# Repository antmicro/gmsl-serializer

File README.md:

# GMSL Serializer Board

Copyright (c) 2023-2025 [Antmicro](https://www.antmicro.com)

## Overview

This project contains open hardware design files for the GMSL Serializer Board.
This board accepts MIPI CSI-2 signals from Antmicro's 50-pin FFC video interface and transmits the video data over GMSL2.
The GMSL Serializer Board is powered over GMSL coaxial cable.

The design files were prepared in KiCad 8.

## Key features

* Input: 4-lane MIPI CSI-2 interface on a 50-pin Antmicro Dual Camera connector
* Output: GMSL2 interface exposed on a FAKRA connector
* PoC filter for sinking power from the GMSL coaxial cable

## Project structure

The main project directory contains KiCad PCB project files, a LICENSE, and a README.
The remaining files are stored in the following directories:

* `doc` - contains schematics
* `assets` - contains visual assets for showcasing the board on Antmicro [Open Hardware Portal](https://openhardware.antmicro.com)

## Licensing

This project is published under the [Apache-2.0](LICENSE) license.

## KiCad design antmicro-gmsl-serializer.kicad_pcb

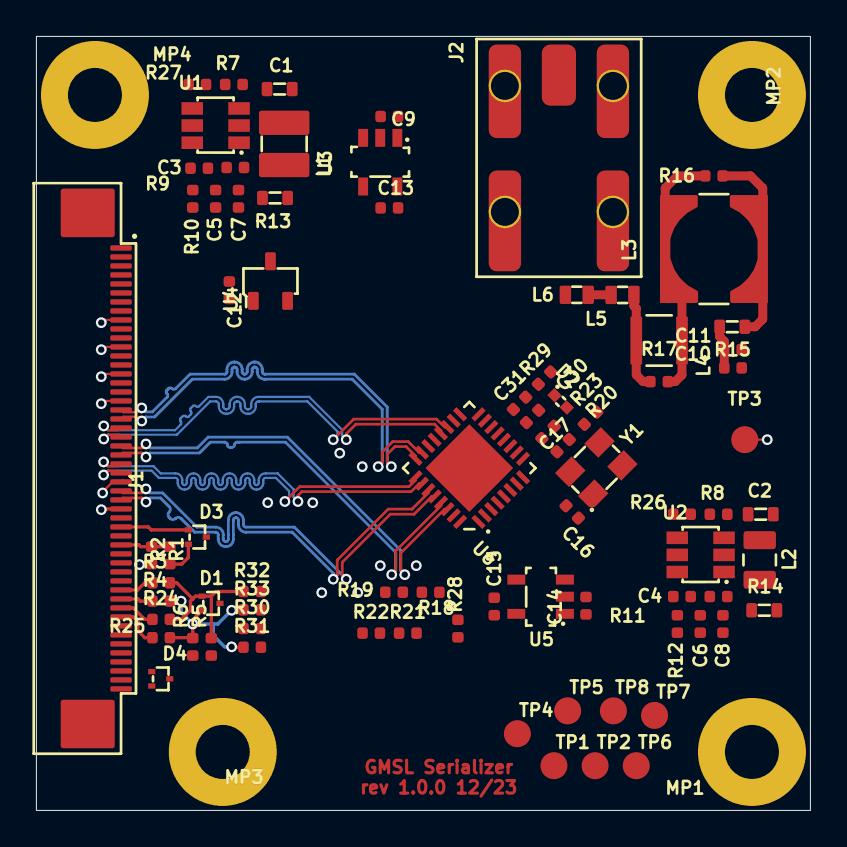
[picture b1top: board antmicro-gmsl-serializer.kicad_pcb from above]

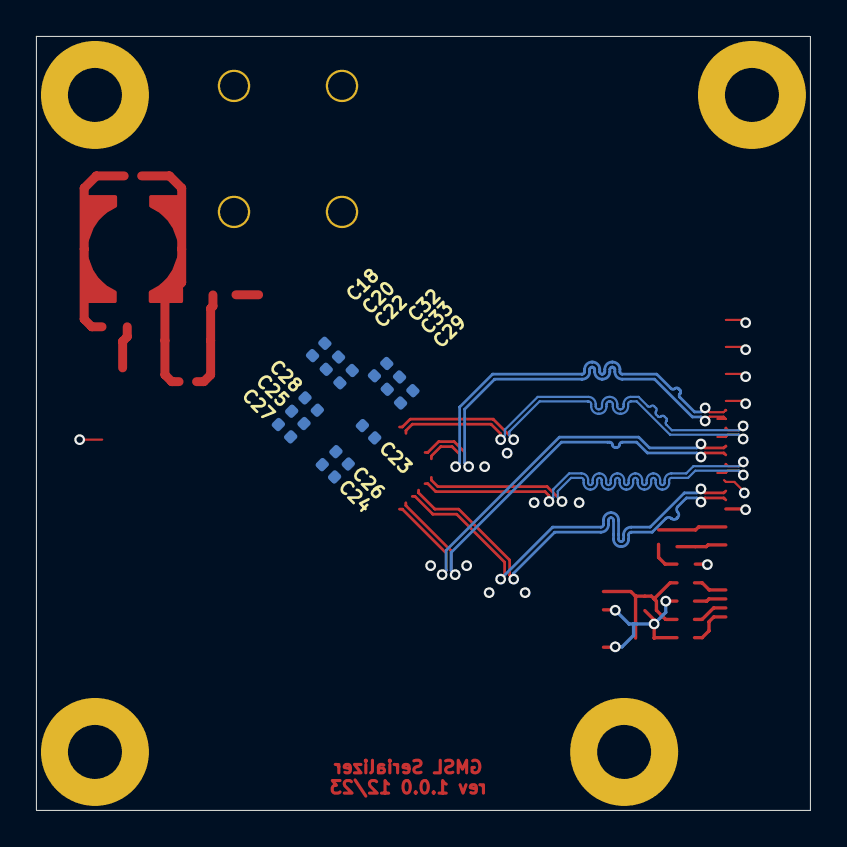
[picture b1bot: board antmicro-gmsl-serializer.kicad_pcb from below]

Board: 4 copper layers, 43.0 x 43.0 mm, 95 parts (12 on the bottom side), 60 nets.

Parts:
C1, C2: C_10u_25V_0603; C_0603_1608Metric
C3: C_220n_0402; C_0402_1005Metric
C4, C10, C20, C22, C24, C30, C31: C_100n_0402; C_0402_1005Metric
C5, C6, C7, C8: C_22u_0402; C_0402_1005Metric
C9, C12, C13, C14, C15: C_1u_16V_0402; C_0402_1005Metric
C11, C23, C27, C28, C29, C32: C_10n_0402; C_0402_1005Metric
C16, C17: C_33p_0402; C_0402_1005Metric
C18, C25, C26, C33: C_10u_0402; C_0402_1005Metric
D1, D3, D4: TPD2E009_SOT-9X3; SOT-723
D2: AXGD10402KR; D_0402_1005Metric
J1: Conn_FFC_WE_68715014022; Conn_FFC_WE_68715014x22
J2: Conn_FAKRA_2FAI-NZSP-PCBB6; Conn_FAKRA_59S2AQ-40MT5-Z_1
L1: L_3u3_3.1A_Bourns-SRP3212A; L_Bourns-SRP3212A
L2: L_1u_2.6A_0806; L_0806_2016Metric
L3: L_22u_1.12A_Coilcraft-MSS6132T; L_Coilcraft-MSS6132T
L4: L_6u8_1A_Coilcraft-1210POC; L_Coilcraft-1210POC
L5, L6: L_470n_1A_Coilcraft-PFL1609; L_Coilcraft-PFL1609
MP1, MP2, MP3, MP4: MP_Pad6mm_Drill3mm
R1, R7, R8, R10, R12, R19, R22, R26, R27, R28: R_10k_0402; R_0402_1005Metric
R2: R_12k_0402; R_0402_1005Metric
R3, R4, R24, R25: R_100R_0402; R_0402_1005Metric
R5, R6: R_4k7_0402; R_0402_1005Metric
R9: R_52k3_0402; R_0402_1005Metric
R11: R_12k4_0402; R_0402_1005Metric
R13, R14, R15: R_0R_22.4A_0603; R_0603_1608Metric
R16, R17: R_5k1_0402; R_0402_1005Metric
R18, R21: R_80k6_0402; R_0402_1005Metric
R20, R30, R31, R32, R33: R_0R_0402; R_0402_1005Metric
R23: R_402R_0402; R_0402_1005Metric
R29: R_51R_0402; R_0402_1005Metric
TP1, TP2, TP3, TP4, TP5, TP6, TP7, TP8: TP_1.5mm_SMD; TP_SMD_1.5mm
U1, U2: AP62301_TSOT; TSOT23-6
U3: NCP163ASN330T1G; SOT-23-5
U4: REF3012AIDBZT; SOT-23-3
U5: TLV73312PDBVT; SOT-23-5
U6: MAX9295A; QFN-32-1EP_5x5mm
Y1: Resonator_25MHz_ABM8G; Oscillator_SMD_Geyer_KX-7-4Pin_3.2x2.5mm

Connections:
+1V2: C15.2, C18.2, C20.2, C22.2, TP5.1, U5.5 (VOUT), U6.15 (VDD)
+1V8: C14.2, C25.2, C27.2, C28.2, R14.2, TP2.1, U5.1 (VIN), U5.3 (EN), U6.11 (VDD_1.8V)
+3V3: C13.2, C29.2, C32.2, C33.2, D4.1, J1.47, J1.48, R5.2, R6.2, R28.2, TP4.1, U3.5 (VOUT), U6.16 (VDDIO)
+5V: C9.2, C12.2, D4.2, J1.49, J1.50, R13.2, TP1.1, U3.1 (VIN), U3.3 (EN), U4.1 (IN)
+12V: C1.2, C2.2, C10.2, C11.2, R7.2, R8.2, R15.1, TP3.1, U1.3 (VIN), U2.3 (VIN)
/Connectors/SCL_CAM0: J1.40, R4.1
/Connectors/SCL_CAM1: J1.42, R25.1
/Connectors/SDA_CAM0: J1.39, R3.1
/Connectors/SDA_CAM1: J1.41, R24.1
/Serializer/CFG0: R18.1, R19.2, U6.3 (MFP1/CFG0)
/Serializer/CFG1: R21.1, R22.2, U6.4 (MFP2/CFG1)
/Serializer/VDDIO: R18.2, R21.2
/Serializer/X1: C16.2, U6.8 (X1/OSC), Y1.1
/Serializer/X2: R20.2, U6.9 (X2)
/Serializer/X2_R: C17.2, R20.1, Y1.3
/Supply/EN_1V8: R8.1, R26.2, U2.5 (EN)
/Supply/EN_5V: R7.1, R27.2, U1.5 (EN)
/Supply/FB_1V8: R11.1, R12.2, U2.4 (FB)
/Supply/FB_5V: R9.1, R10.2, U1.4 (FB)
/Supply/OUT_1V8: C6.2, C8.2, L2.2, R11.2, R14.1
/Supply/OUT_5V: C5.2, C7.2, L1.2, R9.2, R13.1
/Supply/SW_1V8: C4.2, L2.1, U2.2 (SW)
/Supply/SW_5V: C3.2, L1.1, U1.2 (SW)
CSI_CLK_N: J1.28, U6.28 (CK_N)
CSI_CLK_P: J1.29, U6.27 (CK_P)
CSI_D0_N: J1.25, U6.26 (D0_N)
CSI_D0_P: J1.26, U6.25 (D0_P)
CSI_D1_N: J1.23, U6.30 (D1_N)
CSI_D1_P: J1.24, U6.29 (D1_P)
CSI_D2_N: J1.21, U6.20 (D2_N)
CSI_D2_P: J1.22, U6.19 (D2_P)
CSI_D3_N: J1.19, U6.24 (D3_N)
CSI_D3_P: J1.20, U6.23 (D3_P)
GND: C1.1, C2.1, C5.1, C6.1, C7.1, C8.1, C9.1, C10.1, C11.1, C12.1, C13.1, C14.1, C15.1, C16.1, C17.1, C18.1, C20.1, C22.1, C23.1, C24.1, C25.1, C26.1, C27.1, C28.1, C29.1, C32.1, C33.1, D1.3, D2.2, D3.3, D4.3, J1.9, J1.12, J1.15, J1.18, J1.27, J1.30, J1.MP1 (MP), J1.MP2 (MP), J2.2, J2.3, J2.4, J2.5, MP1.1, MP2.1, MP3.1, MP4.1, R2.2, R10.1, R12.1, R19.1, R22.1, R23.1, R26.1, R27.1, R29.1, U1.1 (GND), U2.1 (GND), U3.2 (GND), U4.3 (GND), U5.2 (GND), U6.33 (GND), Y1.2 (SH), Y1.4 (SH)
GPIO3: D3.1, J1.32, U6.17 (MFP3)
GPIO4: D3.2, R1.2, U6.18 (MFP4)
unnamed: C3.1, U1.6 (BST)
unnamed: C4.1, U2.6 (BST)
unnamed: C23.2, C24.2, C26.2, U6.14 (CAP_VDD)
unnamed: C30.1, U6.12 (SIO_P)
unnamed: C31.1, U6.13 (SIO_N)
unnamed: C31.2, R29.2
unnamed: J1.34, R1.1, R2.1
unnamed: L3.1, R15.2, R16.1
unnamed: L3.2, L4.1, R16.2, R17.1
unnamed: L4.2, L5.1, R17.2
unnamed: L5.2, L6.1
unnamed: R23.2, U6.10 (XRES)
unnamed: R28.1, U6.1 (PWDNB)
unnamed: R30.2, U6.31 (MFP7)
unnamed: R31.2, U6.32 (MFP8)
unnamed: R32.2, U6.5 (MFP9)
unnamed: R33.2, U6.6 (MFP10)
unnamed: TP6.1, U6.2 (MFP0)
unnamed: TP7.1, U6.21 (MFP5)
unnamed: TP8.1, U6.22 (MFP6)
SCL: D1.2, R4.2, R6.1, R25.2, R31.1, R33.1
SDA: D1.1, R3.2, R5.1, R24.2, R30.1, R32.1
SIO_P: C30.2, D2.1, J2.1, L6.2
VREF: U4.2 (OUT), U6.7 (VREF)

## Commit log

2023-11-28 Add .gitignore
2024-01-11 Implement changes suggested in design review to schematics
2024-01-11 Import layer stack, add mounting points
2024-01-11 Remove #auto_saved_files#
2024-01-11 Add Antmicro and OShw logos
2024-01-11 Add 1V8 to 1V2 LDO
2024-01-11 Place and route I2C components
2024-01-11 Place and route DC converters
2024-01-11 Add block diagram to schematic
2024-01-11 Change VDDIO to 3V3
2024-01-11 Place and route chip decoupling caps and oscillator
2024-01-11 Add resistor selectable i2c
2024-01-11 Add LICENSE
2024-01-11 Add crystal to the serializer chip
2024-01-11 [WiP]:Add serializer signals and decoupling capacitors
2024-01-11 Add stiching vias and GND planes
2024-01-11 Add I2C protection
2024-01-11 Update stackup
2024-01-11 Route CSI lines
2024-01-11 Add 2V5 VREF
2024-01-11 Add PoC, 5V converter, 1V8 converter
2024-01-11 Import changes from schematic to PCB, place additional components
2024-01-11 Draw board outline, place MPs and 50pin conn
2024-01-11 Add i2c and gpio triggers
2024-01-11 Anotate components and fix ERC errors and warnings
2024-01-11 Add serializer supply filtration
2024-01-11 Add cfg pins handling
2024-01-11 Tune CSI lines
2024-01-11 Change revision on schematic to 1.0.0
2024-01-11 Add 5V -> 3V3 LDO to supply section
2024-01-11 Decrease board size
2024-01-11 Add 50 pin FFC cSI connector
2024-01-11 Add low-capacitance TVS to serial output
2024-01-11 Place and route PoC filter
2024-01-11 Add initial project
2024-01-11 Relocate DC converters and add planes
2024-01-11 Add testpoints to unused MF pins
2024-01-11 Add FAKRA connector
2024-01-11 Reference voltage chip closer to the Vref pin
2024-01-11 Route 12V to 5V DC converter
2024-01-11 Remove R15 and anotate schematic
2024-01-11 Clean DRC
2024-01-11 Route 12V to 1V8 DC converter
2024-01-11 Tune CSI tracks
2024-01-11 Update TVS diodes
2024-01-11 Make power tracks wider
2024-01-11 Round CSI tracks
2024-01-11 [#53377] Rearange supply schematic
2024-01-11 Move gmsl track to the middle of the pad
2024-01-11 Route serializer chip breakout
2024-01-11 Improve decoupling capacitors
2024-01-11 [#53377] Mark 1V25 reference as DNP
2024-01-11 [#52707] PCB: place designators, update footprints, clean ERC
2024-01-11 Make 5V track wider - 1mm)
2024-01-11 Allign schematic components
2024-01-11 Add PCB SHA silkscreen text
2024-01-11 [#53377] Add LDO config register addresses to schematic
2024-01-11 Change default track width 0.125 -> 0.2
2024-01-11 Remove leftover ERC exclusions
2024-01-11 Route I2C
2024-01-11 Update GND plane and date
2024-01-11 Improve layout
2024-01-11 Remove mounting points designators
2024-01-11 Improve L5 connection, improve ground plane
2024-01-11 Move cfg resistors further from CSI lines
2024-01-11 Route low speed signals
2024-01-11 Increase decoupling caps track width
2024-01-11 Add OHP assets
2024-01-12 Add initial README
2024-01-12 Update naming convention
2024-01-12 Add PDF schematic
2024-01-12 README: Add 3D Vis
2024-01-12 Rescale image
2024-02-07 Notes added by 'git notes add'
2024-06-21 [#55438] Add LED indicators to schematics
2024-06-21 [#55438] Place LED indicators on PCB
2024-06-24 [#55438] Update README.md
2024-06-24 [#55438] Add GND testpoint
2024-06-24 [#55438] Update FAKRA connector
2024-07-02 [#55438] Update assets, doc and img
2024-07-02 [#55438] Update components
2024-09-10 [#65118] Update assets
2024-10-04 [#66847] Make schematic hierarchical
2024-10-04 [#66847] Serializer chip: MAX9295A -> MAX96717
2024-10-07 [#66847] unDNP pullups on I2C; update pcb from sch
2024-10-07 [#66847] Update DNP style; Update from lib; Fix CSI bus definition
2024-10-07 [#66847] Change 3V3 LDO; Update L3 footprint
2024-10-07 [#66847] Start improving CSI layout
2024-10-08 [#66847] Tune CSI
2024-10-08 [#66847] Layout improvements
2024-10-08 [#66847] Bump date&rev; Clean ERC
2024-10-08 [#66847] Update config resistors
2024-10-08 [#66847] Show MPN insted value; Update description
2024-10-08 [#66847] Update MAX96717 symbol: flip CSI N/P to match symbol standard
2024-10-08 [#66847] Updated vias
2024-10-08 [#66847] Update assets
2024-11-25 [#69177] Update to Kicad 8
2024-11-25 [#69177] Switched 3V3 suply from LDO to buck converter
2024-11-25 [#69177] Updated layout with new buck converter
2024-11-25 [#69177] Routed changed components
2024-11-25 [#69177] Solved all DRC problems
2024-11-25 [#69177] Updated revision to 1.1.1
2024-11-27 [#69177] Post review fixes
2024-11-27 [#69177] Updated assets and PDF schematics
2024-11-27 [#69177] Tidied up designators in DC-DC area
2024-11-28 [#69177] Update assets
2024-11-28 [#69177] Update README
2025-03-10 [#74135] Standardize netclass names
2025-03-10 [#74135] Update copyright date
2025-03-21 [#74135] Add SI assets

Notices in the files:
parts and their libraries:
License: Apache-2.0
